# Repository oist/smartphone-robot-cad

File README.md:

# CAD for the OIST smartphone robots

This repository contains the CAD files for the OIST smartphone robots.

- [./body](./body) contains standard 3D CAD files used for the robot's 3D printed body.
- [./pcb](./pcb) contains the KiCad files for the robot's PCB and schematic design.

These two subprojects (body and pcb) have direct dependencies on each other as the 3D CAD design is based on the PCB design.
It is likely a good idea to manage the development of each on a separate branch and merge them together when necessary.

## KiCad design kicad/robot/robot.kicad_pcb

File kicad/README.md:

# Cloning the Repo
Currently this repo is an OIST internal repo, so read access is only given to specific users. Add external users for collaboration. 

Note this repo uses a central library management system. Symbols, footprints, and models are maintained on a personal fork of the central kicad library repos. These forks are maintained as submodules within the kicad-symbols, kicad-footprints, and kicad-packages3D respectively under:

[https://github.com/oist/smartphone-robot-cad/tree/main/kicad/](https://github.com/oist/smartphone-robot-cad/tree/main/kicad/)

Those forks should all be public and you should be able to clone the main repo with submodules without additional access, but just in case, here are the links to the forks:
- [https://gitlab.com/topherbuckley/kicad-symbols](https://gitlab.com/topherbuckley/kicad-symbols)
- [https://gitlab.com/topherbuckley/kicad-footprints](https://gitlab.com/topherbuckley/kicad-footprints)
- [https://gitlab.com/topherbuckley/kicad-packages3D](https://gitlab.com/topherbuckley/kicad-packages3D)

The easiest way to clone including all submodules would likely be `git clone --recurse-submodules -j8 git@github.com:oist/smartphone-robot-cad.git' if you are having trouble with that, you can refer to these links for details:

- [StackOverflow](https://stackoverflow.com/questions/3796927/how-do-i-git-clone-a-repo-including-its-submodules)
- [Git Docs](https://git-scm.com/docs/git-submodule)

Note that because of the main repo and submodules are hosted on two different platforms (github and gitlab) you must have credentials for both platforms. You can use your github credentials to setup a gitlab account and add your existing SSH keys to your gitlab account. More on how to do that [here](https://docs.gitlab.com/ee/user/ssh.html)

# Setting up the Environment

KiCAD makes use of user configuration files to define libraries, so without modifying your setup, you will unlikely be able to resolve the majority of libraries used in this project. There are many ways to go about this, of which you can find more details in the links below:

- [Project Collaboration Tips](https://forum.kicad.info/t/project-and-libary-setup-for-sharing-and-collaboration-kicad-version-5/20842/2) (See section Simplify First Time Setup...)

This repo has been set up to make using environmental variables the easiest option. In the `config` directory you will find a subdirectories corresponding to minor version of KiCAD. If you add an environment variable for KICAD_CONFIG_HOME pointing to this `config` directory, KiCAD will use these configuration files rather than the defaults. On Ubuntu 20.04 the default is `~/.config/kicad/`. Note you must then open kicad from a terminal that as properly sourced the newly created environmental variables. In a bash terminal this would be:

```
source KICAD_CONFIG_HOME=[path_to_repo]/config
kicad
```

Note this will use blank (default or empty)  configurations, so feel free to copy/paste your personal configurations into this `config` directory as all files other than `sym-lib-table` and `fp-lib-table` are ignored by the `.gitignore` file. 

# Additional References
- [Good discussion on KiCAD Collaboration and Versioning](https://forum.kicad.info/t/working-collaborately-on-projects-using-git/16114/11)
- [Nice tools for versioning](https://jnavila.github.io/plotkicadsch/)

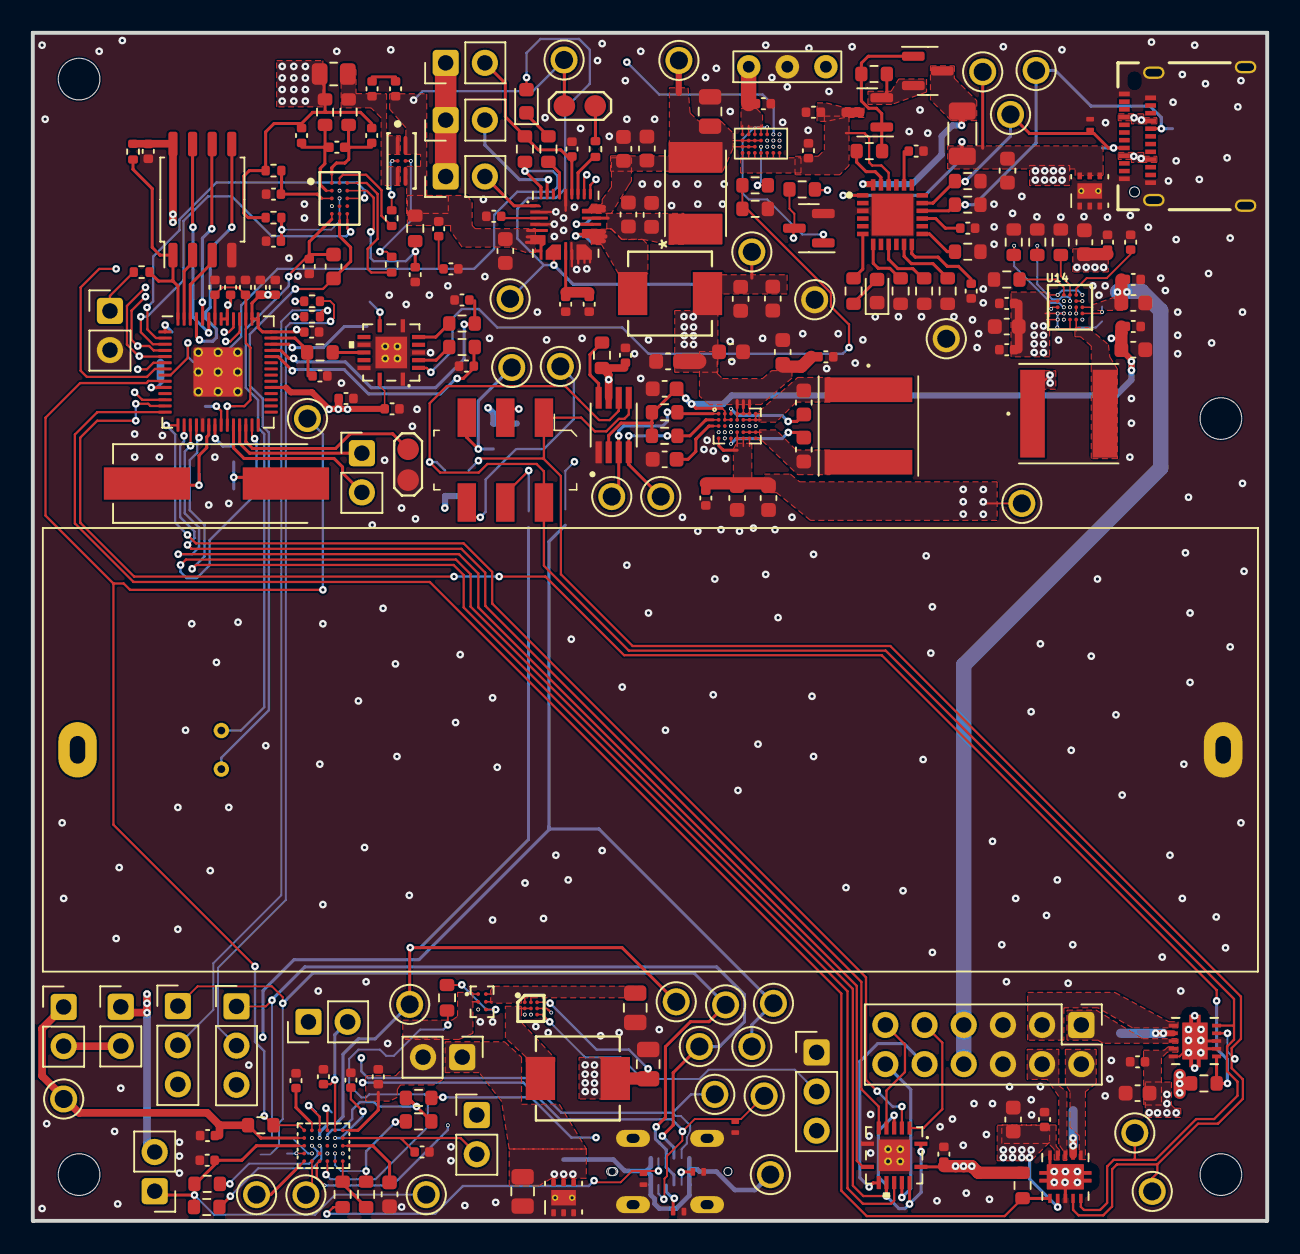
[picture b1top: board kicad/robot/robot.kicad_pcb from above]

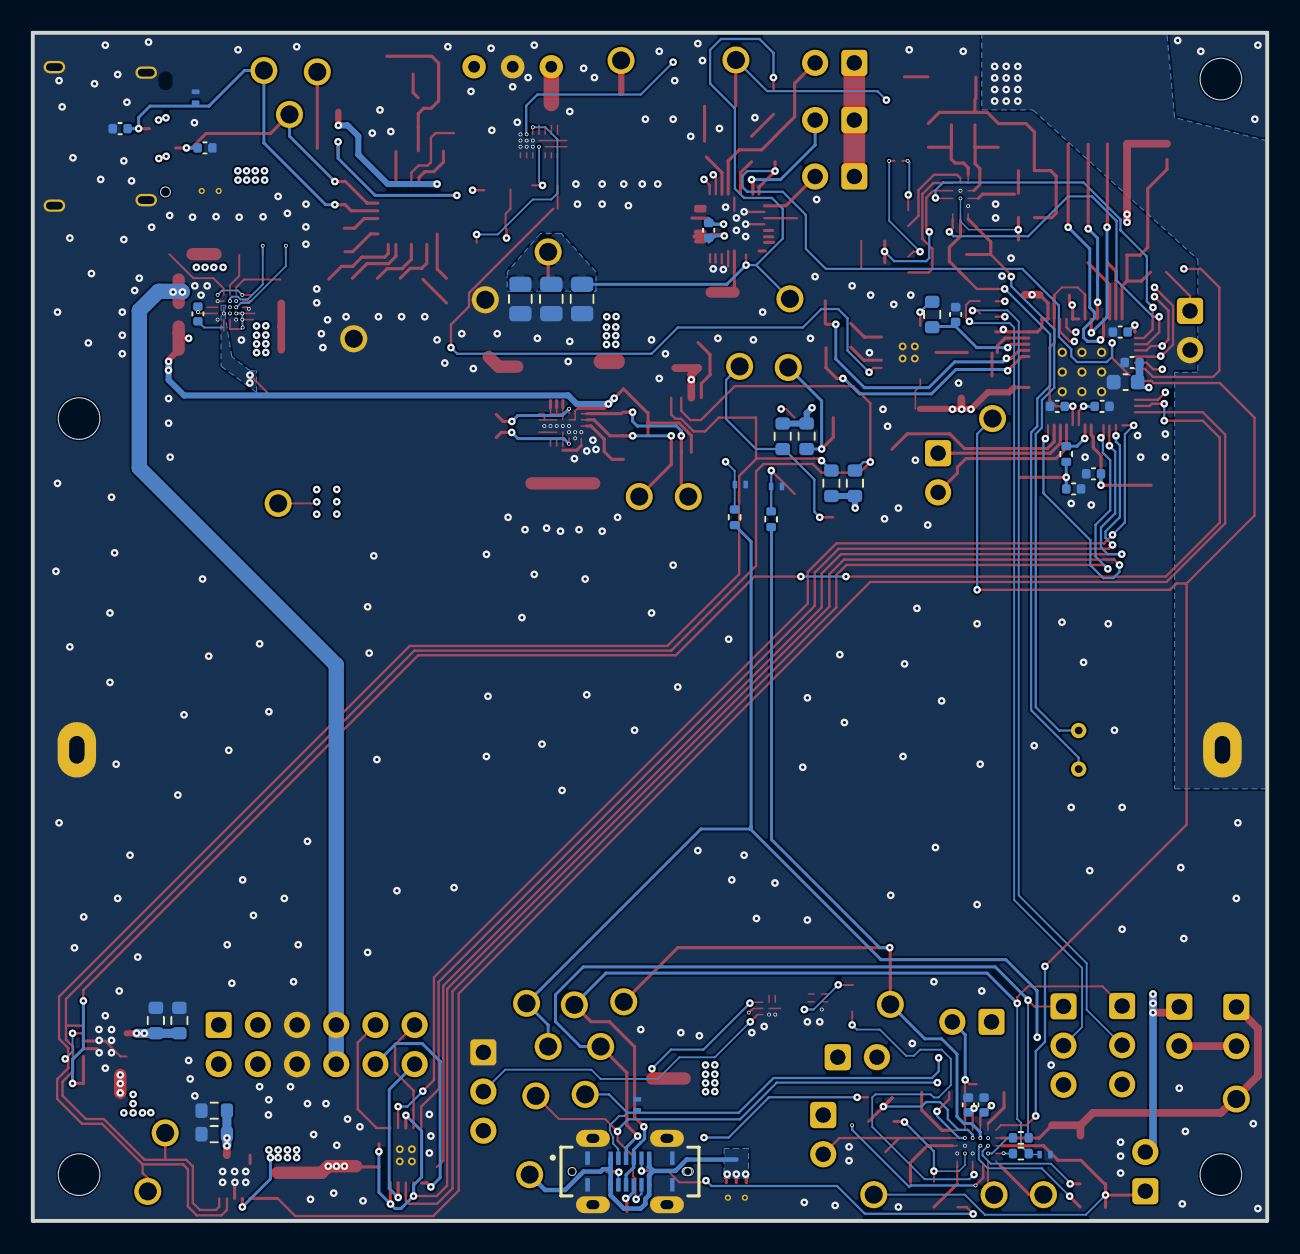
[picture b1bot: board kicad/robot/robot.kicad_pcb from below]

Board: 4 copper layers, 80.0 x 77.0 mm, 268 parts (37 on the bottom side), 159 nets.

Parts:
BT1: DNP; battery26650_holderOnly
BT2: DNP; battery26650
C1, C33, C34, C76, C78, C86, C87, C91, C93: 22uF; C_0603_1608Metric
C2, C3, C18, C19, C45, C46: 27pF; C_0402_1005Metric
C4, C8, C10, C21, C22, C29, C47, C48, C50, C51, C52, C53, C54, C55, C69, C88, C105: 1uF; C_0402_1005Metric
C5, C6, C7, C9, C11, C12, C13, C14, C15, C16, C24, C32, C35, C36, C37, C38, C39, C40, C41, C44, C57, C58, C59, C60, C61, C62, C63, C64, C65, C66, C70, C71, C72, C73, C74, C85, C90, C92, C102, C103, C104: 0.1uF; C_0402_1005Metric
C17, C20, C25, C27, C42, C43, C67, C68, C75, C77, C80: 10uF; C_0603_1608Metric
C23, C97, C100, C101: 4.7uF; C_0805_2012Metric
C26, C56: 0.47uF; C_0603_1608Metric
C28, C49: 2.2uF; C_0603_1608Metric
C30, C31: 0.22uF; C_0603_1608Metric
C81, C82, C83: DNP; C_0805_2012Metric
C84: 10nF; C_0402_1005Metric
D4: LED_B; D_0603_1608Metric_Harvatek
D6: LED_YG; D_0603_1608Metric_Harvatek
D7: D_Schottky; SD2114S040S8R0
H1, H2, H3, H4: MountingHole; MountingHole_2.7mm_M2.5
J1: USBC_Receptacle_SMD_RA; CON_USB3.1-C_RCPT_SMD_RA_ACP_12401610E4#2A
J3: 67996-412HLF; PinHeader_2x06_P2.54mm_Vertical
J4: USB4120-03-C_REVA; GCT_USB4120-03-C_REVA
JP1, JP2, JP3, JP4, JP5, JP6, JP7: Jumper_Bridged; 2.54mm_2pointJumperClosed
JP8, JP9: Jumper_Open; 2.54mm_2pointJumperOpen
JP10, JP11, JP12: Jumper_3_Bridged12; PinHeader_1x03_P2.54mm_Vertical_Pins12Connected
JP13, JP14, JP15, JP16, JP17, JP18, JP19, JP20, JP21, JP22: Jumper; 2.54mm_2pointJumper
L1, L3: 1.5uH; NRS6028T1R5NMGJ
L2, L4: 0.47uH; Vishay-IHLP-2020BZ-FP_1.905x2.79-3D_2.0-0-0-MFG
Q1: Q_NMOS_GDS; SOT-23
Q2: EFC8811R-TF; ON_Semiconductor-568AL-10_2013-O-MFG
Q3, Q4: YJL3416A; SOT-23
Q5, Q6: SN74AHC125RGYR
R1, R5, R46, R47, R50: 1k; R_0402_1005Metric
R2: DNP; R_0402_1005Metric
R3, R4: 27; R_0402_1005Metric
R6, R7, R32, R33, R41, R42: 10; R_0402_1005Metric
R10, R11, R14, R15, R20, R21, R34, R35: 2.2k; R_0603_1608Metric
R16: 510k; R_0603_1608Metric
R17, R49, R59, R60, R61: 100k; R_0603_1608Metric
R18: 47K; R_0603_1608Metric
R19, R36: 200k; R_0603_1608Metric
R22, R23, R24, R25, R58: 100; R_0603_1608Metric
R26, R27: DNP; R_0603_1608Metric
R28, R31, R66: 10k; R_0603_1608Metric
R29, R30: 0.39; R_0603_1608Metric
R37, R39: 649k; R_0603_1608Metric
R38, R40: 120k; R_0603_1608Metric
R43, R45: 200; R_0603_1608Metric
R44: 5m; R_0805_2012Metric
R48: 2k; R_0603_1608Metric
R51: 10m; R_1206_3216Metric
R52: 768k; R_0603_1608Metric
R53: 113K; R_0603_1608Metric
R54: 28k; R_0603_1608Metric
R55: 14k; R_0603_1608Metric
R56: 110; R_0603_1608Metric
R57: 360; R_0603_1608Metric
R62: 45.3k; R_0603_1608Metric
R63, R64: 5.1k; R_0603_1608Metric
R65: 10M; R_0603_1608Metric
S1: JS202011SCQN; Switch_Slide_JS202011SCQN
TH1: DNP; battery26650_thermistor
TP1, TP2, TP3, TP4, TP5, TP6, TP9, TP10, TP11, TP13, TP14, TP15, TP16, TP17, TP18, TP19, TP20, TP21, TP22, TP23, TP24, TP25, TP26, TP29, TP30, TP31, TP32, TP33, TP34, TP36: TP5002; KEYSTONE_5002
TP12, TP28: TP2PinPads; TestPoint_2Pads_Pitch2mm_SMD
TP27, TP35: 2PinHeader; PinHeader_1x02_P2.54mm_Vertical
U1: DNP; WRM483265-10F5-12V-G
U2: W25Q128JVS; SOIC-8_5.23x5.23mm_P1.27mm
U3: RP2040; RP2040-QFN-56
U4: NCP3901
U5: LSF0102DCTR; SOP65P400X130-8N
U6: MAX77857; WLP-35_7x5_2.828x2.028mm
U7, U10, U15, U19, U20, U21, U22, U23, U26, U27: TPD1E05U06; TPD1E05U06DPYR
U8, U9: DRV8830DRCR; IC_DRV8830DRCR
U11: MAX77958EWV+T; MAX77958EWV&plus_T
U12: BQ27742YZFR-G1; Texas_Instruments-YZF0015-0-0-MFG
U13: MAX77976EFD+; MAX77976
U14: MAX77642ANA+; Maxim-N252B2-1-0-A-MFG
U16: fpf1048bucx; BGA6N50P3X2_146X96X62N
U17: TPS61253AYFFT; Texas_Instruments-YFF0009-BGA9C40P3X3_119X129X62
U18: AP33771DKZ-13; AP33771DKZ13
U24, U25: TVS0500DRV; TVS0500DRVR
Y1: ABLS-12.000MHZ-B4-T; Crystal_SMD_HC49-US

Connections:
/1V8: C26.1, C74.1, C86.1, R20.1, R21.1, U5.2 (VREF_A), U6.A2 (VIO), U6.B2 (EN), U6.B3 (EN), U14.D3 (SBB2)
/3V3: C5.1, C9.1, C10.1, C11.1, C12.1, C13.1, C14.1, C15.1, C16.1, C17.1, C24.1, C35.1, C44.1, C92.1, C93.1, JP1.1 (A), JP5.2 (B), JP7.1 (A), JP8.1 (A), JP9.1 (A), JP10.3 (B), Q5.14 (VCC), Q6.14 (VCC), R2.1, R10.1, R11.1, R14.1, R15.1, R18.1, R19.1, R28.1, R31.1, U2.8 (VCC), U3.1 (IOVDD), U3.10 (IOVDD), U3.22 (IOVDD), U3.33 (IOVDD), U3.42 (IOVDD), U3.43 (ADC_AVDD), U3.44 (VREG_IN), U3.48 (USB_VDD), U3.49 (IOVDD), U5.7 (VREF_B), U14.C3 (SBB1)
/5V: C90.1, C91.1, J3.7, J3.8, U14.C5 (SBB0)
/ADC0: Q5.2 (1A), R16.2, R17.1
/Charger/BATT: C63.2, C65.1, C75.1, Q2.4 (SOURCE2), Q2.6 (SOURCE2), R48.1, TP12.2, TP24.1, U13.5 (BATSP), U13.6 (BATT), U13.7 (BATT), U13.8 (BATT)
/Charger/PVDD: C69.1, C70.1, U13.12 (PVDD)
/Charger/V_IN: C23.1, C67.1, C68.1, D7.2 (Anode), TP23.1, U4.B5 (OUT), U4.B6 (OUT), U4.B7 (OUT), U4.C4 (OUT), U4.C5 (OUT), U4.C6 (OUT), U4.C7 (OUT), U13.22 (CHGIN), U13.23 (CHGIN)
/GPIO4: Q1.3 (D), R18.2, U3.6 (GPIO4)
/GPIO5: U3.7 (GPIO5), U4.D2 (VINA_EN/OTG_EN)
/GPIO6: R49.2, U3.8 (GPIO6), U13.32 (IRQB)
/GPIO7: R36.2, TP20.1, U3.9 (GPIO7), U11.A1 (INTB)
/GPIO9: U1.3 (WC_EN), U3.12 (GPIO9)
/GPIO10: R28.2, U3.13 (GPIO10), U8.6 (~FAULT)
/GPIO11: R31.2, U3.14 (GPIO11), U9.6 (~FAULT)
/GPIO12: Q6.3 (1Y), U3.15 (GPIO12)
/GPIO13: Q6.6 (2Y), U3.16 (GPIO13)
/GPIO14: Q6.8 (3Y), U3.17 (GPIO14)
/GPIO15: Q6.11 (4Y), U3.18 (GPIO15)
/GPIO16: Q6.1 (1~OE), Q6.4 (2~OE), Q6.10 (3~OE), Q6.13 (4~OE), U3.27 (GPIO16)
/I2C0_SCL: R15.2, S1.4, TP4.1, U3.3 (GPIO1), U5.6 (B1), U8.10 (SCL), U9.10 (SCL), U12.E3 (SCL)
/I2C0_SDA: R14.2, S1.1, TP3.1, U3.2 (GPIO0), U5.5 (B2), U8.9 (SDA), U9.9 (SDA), U12.C3 (SDA)
/I2C1_SCL: R35.2, U3.5 (GPIO3), U11.C2 (SCL_M), U13.24 (SCL)
/I2C1_SDA: R34.2, U3.4 (GPIO2), U11.C3 (SDA_M), U13.25 (SDA)
/MCU/D+: JP12.2 (C), R3.1
/MCU/D-: JP11.2 (C), R4.1
/MCU/GPIO26_ADC0: C39.1, R25.1, U3.38 (GPIO26_ADC0)
/MCU/GPIO27_ADC1: C38.1, R24.1, U3.39 (GPIO27_ADC1)
/MCU/GPIO28_ADC2: C37.1, R23.1, U3.40 (GPIO28_ADC2)
/MCU/GPIO29_ADC3: C36.1, R22.1, U3.41 (GPIO29_ADC3)
/MCU/QSPI_SCLK: U2.6 (CLK), U3.52 (QSPI_SCLK)
/MCU/QSPI_SD0: U2.5 (DI(IO0)), U3.53 (QSPI_SD0)
/MCU/QSPI_SD1: U2.2 (DO(IO1)), U3.55 (QSPI_SD1)
/MCU/QSPI_SD2: U2.3 (IO2), U3.54 (QSPI_SD2)
/MCU/QSPI_SD3: U2.7 (IO3), U3.51 (QSPI_SD3)
/MCU/QSPI_SS: R1.1, R2.2, U2.1 (~CS), U3.56 (QSPI_SS)
/MCU/RUN: TP28.1, U3.26 (RUN)
/MCU/SWCLK: TP27.2, U3.24 (SWCLK)
/MCU/SWD: TP27.1, U3.25 (SWD)
/MCU/XIN: C2.1, U3.20 (XIN), Y1.1
/MCU/XOUT: R5.1, U3.21 (XOUT)
/MCU/~USB_BOOT: R1.2, TP35.1
/MOTORS/ENC_11: J3.9, Q6.2 (1A)
/MOTORS/ENC_12: J3.11, Q6.5 (2A)
/MOTORS/ENC_21: J3.10, Q6.9 (3A)
/MOTORS/ENC_22: J3.12, Q6.12 (4A)
/MOTORS/OUT_N1: J3.3, U8.1 (OUT2)
/MOTORS/OUT_N2: J3.2, U9.1 (OUT2)
/MOTORS/OUT_P1: J3.1, U8.3 (OUT1)
/MOTORS/OUT_P2: J3.4, U9.3 (OUT1)
/PowerMux/FLAG: Q1.1 (G), U4.D3 (VINB_EN/FLAG)
/PowerMux/VIN_A: C21.1, C105.1, Q4.3 (D), U4.A1 (VINA), U4.A2 (VINA), U4.A3 (VINA), U4.A4 (VINA), U4.A5 (VINA), U4.A6 (VINA), U4.A7 (VINA), U18.22 (VBUS)
/PowerMux/VIN_B: C22.1, U1.1 (Vchar_IN), U4.D4 (VINB), U4.D5 (VINB), U4.D6 (VINB), U4.D7 (VINB)
/SCL_EXT: R11.2, S1.6, TP6.1
/SCL_SL: R7.1, TP2.1, TP19.1, U11.B3 (SDA)
/SDA_EXT: R10.2, S1.3, TP5.1
/SDA_SL: R6.1, TP1.1, TP18.1, U11.B2 (SCL)
/SYS: C1.1, C4.1, C25.1, C27.1, C29.2, C76.1, C78.1, C81.1, C82.1, C83.1, C85.1, C87.1, C101.1, D6.2 (A), JP2.1 (A), JP3.1 (A), L2.2, L4.1, TP25.1, TP36.1, U6.A4 (IN), U6.A5 (IN), U6.A6 (IN), U6.B4 (IN), U13.9 (SYS), U13.10 (SYS), U13.11 (SYS), U14.A1 (SYSA), U14.A5 (IN_LDO), U14.B1 (SYSA), U14.D1 (EN1), U14.D2 (EN0), U14.E1 (EN2), U14.E3 (IN_SBB), U17.A3 (VIN)
/USB-PD-ExtChg/CC1: C18.1, J1.A5 (CC1), R63.1, TP9.1, U18.17 (CC1), U26.1 (I/O)
/USB-PD-ExtChg/CC2: C19.1, J1.B5 (CC2), R64.1, TP10.1, U18.16 (CC2), U27.1 (I/O)
/USB-PD-PhonePC/DN_EXT: J4.A7 (Dn1), J4.B7 (Dn2), JP11.1 (A), R32.1, TP13.1, U15.1 (I/O)
/USB-PD-PhonePC/DN_Switched: JP11.3 (B), TP16.1, U11.E1 (DN1)
/USB-PD-PhonePC/DP2_Switched: JP12.3 (B), TP17.1, U11.E2 (DP2)
/USB-PD-PhonePC/DP_EXT: J4.A6 (Dp1), J4.B6 (Dp2), JP12.1 (A), R33.1, TP14.1, U19.1 (I/O)
/USB-PD-PhonePC/GPIO0: R37.2, R38.1, U11.E6 (GPIO0)
/USB-PD-PhonePC/GPIO1: R39.2, R40.1, U11.B4 (GPIO1)
/USB-PD-PhonePC/GPIO3: R37.1, R39.1, U11.D5 (GPIO3)
/USB-PD-PhonePC/GPIO4: R65.2, U11.E4 (GPIO4)
/USB-PD-PhonePC/GPIO5: U11.E3 (GPIO5), U17.B3 (EN)
/USB-PD-PhonePC/VIO1: JP1.2 (B), JP6.2 (B)
/USB-PD-PhonePC/VIO1_: C54.1, JP6.1 (A), R36.1, TP22.1, U11.B1 (VIO1)
/USB-PD-PhonePC/VIO2_: C53.1, JP5.1 (A), R34.1, R35.1, TP21.1, U11.C1 (VIO2)
/VBoost: C32.2, C33.2, C34.2, C40.1, C41.1, C42.1, C43.1, TP34.1, U6.D4 (OUT), U6.E1 (FB), U6.E4 (OUT), U6.E5 (OUT), U6.E6 (OUT), U8.4 (VCC), U9.4 (VCC), U9.7 (A0)
GND: BT1.2 (-), C1.2, C2.2, C3.2, C4.2, C5.2, C6.2, C7.2, C8.2, C9.2, C10.2, C11.2, C12.2, C13.2, C14.2, C15.2, C16.2, C17.2, C18.2, C19.2, C20.2, C21.2, C22.2, C23.2, C24.2, C25.2, C26.2, C27.2, C28.2, C29.1, C32.1, C33.1, C34.1, C35.2, C36.2, C37.2, C38.2, C39.2, C40.2, C41.2, C42.2, C43.2, C44.2, C45.2, C46.2, C47.2, C48.2, C49.2, C50.2, C51.2, C52.2, C53.2, C54.2, C55.2, C57.2, C58.2, C64.2, C66.2, C67.2, C68.2, C69.2, C70.2, C71.2, C72.2, C74.2, C75.2, C76.2, C77.2, C78.2, C80.2, C81.2, C82.2, C83.2, C85.2, C86.2, C87.2, C88.2, C90.2, C91.2, C92.2, C93.2, C97.2, C100.2, C101.2, C102.2, C103.2, C104.2, C105.2, D4.1 (K), J1.25 (SHLD), J1.A1 (GND), J1.A12 (GND), J1.B1 (GND), J1.B12 (GND), J3.5, J3.6, J4.A1 (GND), J4.A12 (GND), J4.B1 (GND), J4.B12 (GND), J4.SHELL, JP10.1 (A), Q1.2 (S), Q5.1 (1~OE), Q5.4 (2~OE), Q5.7 (GND), Q5.10 (3~OE), Q5.13 (4~OE), Q5.PAD (GND), Q6.7 (GND), Q6.PAD (GND), R17.2, R26.2, R27.2, R29.2, R30.2, R52.2, R53.2, R54.2, R55.2, R59.1, R60.1, R61.1, R62.2, R63.2, R64.2, TP26.1, TP28.2, TP33.1, TP35.2, U1.2 (GND), U2.4 (GND), U3.19 (TESTEN), U3.57 (GND), U4.B1 (GND), U4.B2 (GND), U4.B3 (GND), U4.C1 (MODE), U4.C2 (GND), U4.C3 (GND), U4.D1 (CRTL), U5.1 (GND), U6.C3 (PGND), U6.C4 (PGND), U6.C5 (PGND), U6.C6 (PGND), U6.C7 (PGND), U6.D1 (SEL), U6.D2 (PGND), U6.D3 (PGND), U6.E2 (AGND), U7.2 (GND), U8.5 (GND), U8.7 (A0), U8.8 (A1), U8.11 (GND), U9.5 (GND), U9.8 (A1), U9.11 (GND), U10.2 (GND), U11.C5 (GND_A), U11.D4 (GPIO6_I2C_ADDR), U11.D6 (GND_D), U12.B2 (NC), U12.D1 (VSS), U13.2 (THM), U13.4 (BATSN), U13.13 (DGND), U13.14 (PGND), U13.15 (PGND), U13.16 (PGND), U13.28 (AGND), U14.B2 (RSET_LDO), U14.B4 (GND), U14.B5 (GND), U14.C1 (ENLDO), U14.E2 (GND), U14.E5 (PGND), U15.2 (GND), U16.C1 (GND), U17.C1 (GND), U17.C2 (GND), U18.3 (GND), U18.25 (EP), U19.2 (GND), U20.2 (GND), U21.2 (GND), U22.2 (GND), U23.2 (GND), U24.1 (GND), U24.2 (GND), U24.3 (GND), U24.7 (GND), U25.1 (GND), U25.2 (GND), U25.3 (GND), U25.7 (GND), U26.2 (GND), U27.2 (GND)
unnamed: BT1.1 (+), C59.2, C61.1, R41.1, R42.1, R43.2, R44.2
unnamed: C3.1, R5.2, Y1.2
unnamed: C6.1, C7.1, C8.1, U3.23 (DVDD), U3.45 (VREG_VOUT), U3.50 (DVDD)
unnamed: C20.1, J1.A4 (VBUS), J1.A9 (VBUS), J1.B4 (VBUS), J1.B9 (VBUS), R51.1, TP11.1, U18.1 (ISENP), U25.4 (IN), U25.5 (IN), U25.6 (IN)
unnamed: C28.1, U6.C1 (VL)
unnamed: C30.1, U6.A3 (BST1)
unnamed: C30.2, L1.1, U6.A7 (LX1), U6.B5 (LX1), U6.B6 (LX1), U6.B7 (LX1)
unnamed: C31.1, L1.2, U6.D5 (LX2), U6.D6 (LX2), U6.D7 (LX2), U6.E7 (LX2)
unnamed: C31.2, U6.E3 (BST2)
unnamed: C45.1, J4.B5 (CC2), TP29.1, U11.A4 (CC2), U22.1 (I/O)
unnamed: C46.1, J4.A5 (CC1), TP15.1, U11.A3 (CC1), U23.1 (I/O)
unnamed: C47.1, JP2.2 (B), U11.A5 (VCIN)
unnamed: C48.1, JP3.2 (B), U11.B6 (SYS)
unnamed: C49.1, U11.C6 (AVL)
unnamed: C50.1, JP4.2 (B), U11.A6 (VBUS), U16.A1 (VOUT), U16.B1 (VOUT)
unnamed: C51.1, U11.A2 (VDD1P1)
unnamed: C52.1, U11.B5 (VDD1P8)
unnamed: C55.1, C56.1, TH1.1, U12.E1 (REG25)
unnamed: C56.2, TH1.2, U12.E2 (TS)
unnamed: C57.1, R42.2, U12.C2 (BAT)
unnamed: C58.1, R41.2, U12.C1 (VPWR)
unnamed: C59.1, C60.1, R43.1, U12.B1 (SRN)
unnamed: C60.2, C61.2, R45.1, U12.A1 (SRP)
unnamed: C62.1, Q2.1 (SOURCE1), Q2.3 (SOURCE1), R44.1, R45.2
unnamed: C62.2, C63.1
unnamed: C64.1, R48.2, U12.B3 (PACKP)
unnamed: C65.2, C66.1
unnamed: C71.1, JP7.2 (B), R49.1, U13.27 (VIO)
unnamed: C72.1, U13.3 (VDD)
unnamed: C73.1, U13.20 (BST)
unnamed: C73.2, L2.1, U13.17 (LX), U13.18 (LX), U13.19 (LX)
unnamed: C77.1, C80.1, D7.1 (Cathode), U13.21 (BYP)
unnamed: C84.1, L3.1, U14.C4 (LXB), U14.D4 (LXB)
unnamed: C84.2, U14.D5 (BST)
unnamed: C88.1, U14.A4 (LDO)
unnamed: C97.1, J4.A4 (VBUS), J4.A9 (VBUS), J4.B4 (VBUS), J4.B9 (VBUS), JP4.1 (A), TP30.1, U24.4 (IN), U24.5 (IN), U24.6 (IN)
unnamed: C100.1, U16.A2 (VIN), U16.B2 (VIN), U17.A1 (VOUT), U17.A2 (VOUT)
unnamed: C102.1, U18.12 (V3VD)
unnamed: C103.1, U18.20 (V5V)
unnamed: C104.1, U18.15 (IFB)
unnamed: D4.2 (A), R57.2
unnamed: D6.1 (K), R56.1
unnamed: J4.A8 (SBU1), R38.2, U21.1 (I/O)
unnamed: J4.B8 (SBU2), R40.2, U20.1 (I/O)
unnamed: JP8.2 (B), U13.31 (SUSPND)
unnamed: JP9.2 (B), U13.1 (DISQBAT)
unnamed: JP10.2 (C), U17.C3 (MODE)
unnamed: L3.2, U14.E4 (LXA)
unnamed: L4.2, U17.B1 (SW), U17.B2 (SW)
unnamed: Q2.2 (GATE1), R46.1
unnamed: Q2.5 (GATE2), R47.1
unnamed: Q3.1 (G), Q4.1 (G), R58.1, R66.2
unnamed: Q3.2 (S), Q4.2 (S), R66.1
unnamed: Q3.3 (D), R51.2, U18.24 (VCC)
unnamed: Q5.3 (1Y), R25.2
unnamed: Q5.6 (2Y), R24.2
unnamed: Q5.8 (3Y), R23.2
unnamed: Q5.11 (4Y), R22.2
unnamed: R3.2, U3.47 (USB_DP)
unnamed: R4.2, U3.46 (USB_DM)
unnamed: R6.2, S1.2, U7.1 (I/O)
unnamed: R7.2, S1.5, U10.1 (I/O)
unnamed: R16.1, U4.B4 (VINA_S)
unnamed: R19.2, U5.8 (EN)
unnamed: R20.2, TP32.1, U5.4 (A2), U6.B1 (SDA)
unnamed: R21.2, TP31.1, U5.3 (A1), U6.A1 (SCL)
unnamed: R26.1, R29.1, U8.2 (ISENSE)
unnamed: R27.1, R30.1, U9.2 (ISENSE)
unnamed: R32.2, U11.D1 (DN)
unnamed: R33.2, U11.D2 (DP)
unnamed: R46.2, U12.A2 (CHG)
unnamed: R47.2, U12.A3 (DSG)
unnamed: R50.1, U13.26 (EXTSM)
unnamed: R50.2, TP12.1
unnamed: R52.1, U14.B3 (RSET_SBB0)
unnamed: R53.1, U14.A3 (RSET_SBB1)
unnamed: R54.1, U14.A2 (RSET_SBB2)
unnamed: R55.1, U14.C2 (RSET_IPK)
unnamed: R56.2, U13.29 (STAT)
unnamed: R57.1, U18.6 (GPIO4)
unnamed: R58.2, U18.23 (PWR_EN)
unnamed: R59.2, U18.7 (VSEL1)
unnamed: R60.2, U18.9 (VSEL0)
unnamed: R61.2, U18.11 (VSEL2)
unnamed: R62.1, U18.13 (PSEL)
unnamed: R65.1, U16.C2 (ON)

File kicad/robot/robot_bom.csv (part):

Ref	Qty Single Board	Batch Size	Qty Total Batch	Stock	Spares	Total+Spares	Sending	Need to Buy	Value	Manufacturer	Part Number	Description	Footprint	Type
Q5,Q6	2	5	10	50	1	11	50	0	SN74AHC125RGYR	Texas Instruments	SN74AHC125RGYR	Buffer/Line Driver 4-CH Non-Inverting 3-ST CMOS 14-Pin VQFN EP T/R	Ultra_Librarian:SN74AHC125RGYR	
U8,U9	2	5	10	30	1	11	25	0	DRV8830DRCR	Texas Instruments	DRV8830DRCR	DC Motor Driver I2C Control	Snapeda:IC_DRV8830DRCR	
Q2	1	5	5	25	1	6	25	0	EFC8811R-TF	ON Semiconductor	EFC8811R-TF	EFC8811R-TF	custom_transistors:ON_Semiconductor-568AL-10_2013-O-MFG	
U4	1	5	5	25	1	6	25	0	NCP3901	onsemi	NCP3901		custom_modules:NCP3901	
U5	1	5	5	25	1	6	25	0	LSF0102DCTR	Texas Instruments	LSF0102DCTR	Dual bidirectional multi-voltage level translator	Snapeda:SOP65P400X130-8N	
U6	1	5	5	25	1	6	25	0	MAX77857	Maxim	MAX77857		Package_BGA:WLP-35_7x5_2.828x2.028mm	
U11	1	5	5	25	1	6	25	0	MAX77958EWV+T	Maxim	MAX77958EWV+T	USB-PD Controller	Ultra_Librarian:MAX77958EWV&plus_T	
U12	1	5	5	25	1	6	25	0	BQ27742YZFR-G1	Texas Instruments	BQ27742YZFR-G1	BQ27742YZFR-G1	Package_BGA:Texas_Instruments-YZF0015-0-0-MFG	
U13	1	5	5	25	1	6	25	0	MAX77976EFD+	Maxim	MAX77976EFD+		Ultra_Librarian:MAX77976	
U14	1	5	5	25	1	6	25	0	MAX77642ANA+	Maxim	MAX77642ANA+	MAX77642ANA+	Package_BGA:Maxim-N252B2-1-0-A-MFG	
U18	1	5	5	25	1	6	25	0	AP33771DKZ-13	Diodes Inc.	AP33771DKZ-13	Diodes Inc. ACDC Decoder W-QFN4040-24 T&R 3K	Package_DFN_QFN:AP33771DKZ13	
BT1	0	5	0	0	0	0		0	DNP	Uxcell	a15042300ux0145		custom_modules:battery26650_holderOnly	
BT2	0	5	0	0	0	0		0	DNP	Suprise Collection	26650-5000-1	Single-cell battery	custom_modules:battery26650	
C1,C33,C34,C76,C78,C86,C87,C91,C93	9	5	45	0	5	50		45	22uF	Murata	GRM188R61A226ME15D	Unpolarized capacitor	Capacitor_SMD:C_0603_1608Metric	
C2,C3,C18,C19,C45,C46	6	5	30	0	3	33		30	27pF	Murata	GRM1555C1H270JA01J	Unpolarized capacitor	Capacitor_SMD:C_0402_1005Metric	
C4,C8,C10,C21,C22,C29,C47,C48,C50,C51,C52,C53,C54,C55,C69,C88,C105	17	5	85	0	9	94		85	1uF	Murata	GRM155R61E105KA12D	Unpolarized capacitor	Capacitor_SMD:C_0402_1005Metric	
C5,C6,C7,C9,C11,C12,C13,C14,C15,C16,C24,C32,C35,C36,C37,C38,C39,C40,C41,C44,C57,C58,C59,C60,C61,C62,C63,C64,C65,C66,C70,C71,C72,C73,C74,C85,C90,C92,C102,C103,C104	41	5	205	0	21	226		205	0.1uF	Samsung	CL05A104KA5NNNC	Unpolarized capacitor	Capacitor_SMD:C_0402_1005Metric	
C17,C20,C25,C27,C42,C43,C67,C68,C75,C77,C80	11	5	55	0	6	61		55	10uF	Murata	GRM188R61E106KA73J	Unpolarized capacitor	Capacitor_SMD:C_0603_1608Metric	
C23,C97,C100,C101	4	5	20	0	2	22		20	4.7uF	Samsung	CL21A475KAQNNNG	Unpolarized capacitor	Capacitor_SMD:C_0805_2012Metric	
C26,C56	2	5	10	0	1	11		10	0.47uF	Samsung	CL10B474KO8NNNC	Unpolarized capacitor	Capacitor_SMD:C_0603_1608Metric	
C28,C49	2	5	10	0	1	11		10	2.2uF	Samsung	CL10A225KP8NNNC	Unpolarized capacitor	Capacitor_SMD:C_0603_1608Metric	
C30,C31	2	5	10	0	1	11		10	0.22uF	Samsung	CL10B224KA8NNNC	Unpolarized capacitor	Capacitor_SMD:C_0603_1608Metric	
C79	0	5	0	0	0	0		0	DNP	DNP	DNP	Unpolarized capacitor	Capacitor_SMD:C_0805_2012Metric	
C84	1	5	5	0	1	6		5	10nF	Samsung	CL05B103KA5NNNC	Unpolarized capacitor	Capacitor_SMD:C_0402_1005Metric	
D4	1	5	5	0	1	6		5	LED_B	Harvatek	B0211NB--02D000114U1930	Light emitting diode	Diode_SMD:D_0603_1608Metric_Harvatek	
D6	1	5	5	0	1	6		5	LED_YG	Harvatek	B1911UYG-20D000114U1930	Light emitting diode	Diode_SMD:D_0603_1608Metric_Harvatek	
D7	1	5	5	0	1	6		5	D_Schottky	KYOCERA AVX	SD2114S040S8R0		Diode_SMD:SD2114S040S8R0	
H1,H2,H3,H4	4	5	20	0	2	22		20	MountingHole	N/A	N/A	Mounting Hole without connection	MountingHole:MountingHole_2.7mm_M2.5	
J1	1	5	5	0	1	6		5	USBC_Receptacle_SMD_RA	Amphenol Commercial Products	12401610E4#2A		AltiumImports:CON_USB3.1-C_RCPT_SMD_RA_ACP_12401610E4#2A	
J3	1	5	5	0	1	6		5	67996-412HLF	Amphenol ICC (FCI)	67996-412HLF	CONN HEADER VERT 12POS 2.54MM	Connector_PinHeader_2.54mm:PinHeader_2x06_P2.54mm_Vertical	
J4	1	5	5	0	1	6		5	USB4120-03-C_REVA	GCT	USB4120-03-C		Connector_USB:GCT_USB4120-03-C_REVA	
JP1,JP2,JP3,JP4,JP5,JP6,JP7	7	5	35	0	4	39		35	Jumper_Bridged	Adam Tech	PH1-02-UA	Jumper, 2-pole, closed/bridged	custom_connectors:2.54mm_2pointJumperClosed	
JP8,JP9	2	5	10	0	1	11		10	Jumper_Open	Adam Tech	PH1-02-UA	Jumper, 2-pole, open	custom_connectors:2.54mm_2pointJumperOpen	
JP10,JP11,JP12	3	5	15	0	2	17		15	Jumper_3_Bridged12	Molex	22-28-4030	Jumper, 3-pole, pins 1+2 closed/bridged	Connector_PinHeader_2.54mm:PinHeader_1x03_P2.54mm_Vertical_Pins12Connected	
JP13,JP14,JP15,JP16,JP17,JP18,JP19,JP20,JP21,JP22	10	5	50	0	5	55		50	Jumper	Sullins	QPC02SXGN-RC	Mechanical Jumper	custom_connectors:2.54mm_2pointJumper	
L1,L3	2	5	10	0	1	11		10	1.5uH	TAIYO YUDEN	NRS6028T1R5NMGJ	Inductor	custom_inductors:NRS6028T1R5NMGJ	
L2,L4	2	5	10	0	1	11		10	0.47uH	Vishay	IHLP2020BZERR47M01	Inductor symbol for simulation only	custom_inductors:Vishay-IHLP-2020BZ-FP_1.905x2.79-3D_2.0-0-0-MFG	
Q1	1	5	5	0	1	6		5	Q_NMOS_GDS	Toshiba	T2N7002AK,LM	N-MOSFET transistor, gate/source/drain	Package_TO_SOT_SMD:SOT-23	
Q3,Q4	2	5	10	0	1	11		10	YJL3416A	Yangjie Electronic Technology 	YJL3416A	20V Vds, 0.63 Id, N-Channel MOSFET with ESD protection, SOT-523	Package_TO_SOT_SMD:SOT-23	
R1,R5,R46,R47,R50	5	5	25	0	3	28		25	1k	Walsin Technologies	WR04X102 JTL	Resistor	Resistor_SMD:R_0402_1005Metric	
R3,R4	2	5	10	0	1	11		10	27	Stackpole Electronics	RMCF0402JT27R0	Resistor	Resistor_SMD:R_0402_1005Metric	
R6,R7,R32,R33,R41,R42	6	5	30	0	3	33		30	10	Yageo	RC0402FR-1310RL	Resistor	Resistor_SMD:R_0402_1005Metric	
R10,R11,R14,R15,R20,R21,R34,R35	8	5	40	0	4	44		40	2.2k	Stackpole Electronics	RMCF0603JT2K20	Resistor	Resistor_SMD:R_0603_1608Metric	
R16	1	5	5	0	1	6		5	510k	Stackpole Electronics	RMCF0603JT510K	Resistor	Resistor_SMD:R_0603_1608Metric	
R17,R49,R59,R60,R61	5	5	25	0	3	28		25	100k	Stackpole Electronics	RMCF0603JG100K	Resistor	Resistor_SMD:R_0603_1608Metric	
R18	1	5	5	0	1	6		5	47K	Stackpole Electronics	RMCF0603JT47K0	Resistor	Resistor_SMD:R_0603_1608Metric	
R19,R36	2	5	10	0	1	11		10	200k	Stackpole Electronics	RMCF0603JT200K	Resistor	Resistor_SMD:R_0603_1608Metric	
R22,R23,R24,R25,R58	5	5	25	0	3	28		25	100	Stackpole Electronics	RMCF0603JT100R	Resistor	Resistor_SMD:R_0603_1608Metric	
R28,R31,R66	3	5	15	0	2	17		15	10k	Stackpole Electronics	RMCF0603JT10K0	Resistor	Resistor_SMD:R_0603_1608Metric	
R29,R30	2	5	10	0	1	11		10	0.39	Panasonic	ERJ-3RQJR39V	Resistor	Resistor_SMD:R_0603_1608Metric	
R37,R39	2	5	10	0	1	11		10	649k	Stackpole Electronics	RMCF0603FT649K	Resistor	Resistor_SMD:R_0603_1608Metric	
R38,R40	2	5	10	0	1	11		10	120k	Stackpole Electronics	RMCF0603JT120K	Resistor	Resistor_SMD:R_0603_1608Metric	
R43,R45	2	5	10	0	1	11		10	200	Bourns	CR0402-JW-201GLF	Resistor	Resistor_SMD:R_0603_1608Metric	
R44	1	5	5	0	1	6		5	5m	Yageo	PA0805FRF470R005L	Resistor	Resistor_SMD:R_0805_2012Metric	
R48	1	5	5	0	1	6		5	2k	Stackpole Electronics	RMCF0603FT2K00	Resistor	Resistor_SMD:R_0603_1608Metric	
R51	1	5	5	0	1	6		5	10m	Panasonic	ERJ-8CWJR010V	Resistor	Resistor_SMD:R_1206_3216Metric	
R52	1	5	5	0	1	6		5	768k	Stackpole Electronics	RMCF0603FT768K	Resistor	Resistor_SMD:R_0603_1608Metric	
R53	1	5	5	0	1	6		5	113K	Stackpole Electronics	RMCF0603FT113K	Resistor	Resistor_SMD:R_0603_1608Metric	
R54	1	5	5	0	1	6		5	28k	Stackpole Electronics	RMCF0603FT28K0	Resistor	Resistor_SMD:R_0603_1608Metric	
R55	1	5	5	0	1	6		5	14k	Stackpole Electronics	RMCF0603FT14K0	Resistor	Resistor_SMD:R_0603_1608Metric	
R56	1	5	5	0	1	6		5	110	Yageo	RC0603JR-07110RL	Resistor	Resistor_SMD:R_0603_1608Metric	
R57	1	5	5	0	1	6		5	360	Stackpole Electronics, Inc.	RMCF0603JT360R	Resistor	Resistor_SMD:R_0603_1608Metric	
R62	1	5	5	0	1	6		5	45.3k	Stackpole Electronics	RMCF0603FT45K3	Resistor	Resistor_SMD:R_0603_1608Metric	
R63,R64	2	5	10	0	1	11		10	5.1k	Stackpole Electronics	RMCF0603JT5K10	Resistor	Resistor_SMD:R_0603_1608Metric	
R65	1	5	5	0	1	6		5	10M	Yageo	AC0603JR-0710ML	Resistor	Resistor_SMD:R_0603_1608Metric	
S1	1	5	5	0	1	6		5	JS202011SCQN	C&K	JS202011SCQN	SWITCH SLIDE DPDT 300MA 6V	Button_Switch_SMD:Switch_Slide_JS202011SCQN	
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
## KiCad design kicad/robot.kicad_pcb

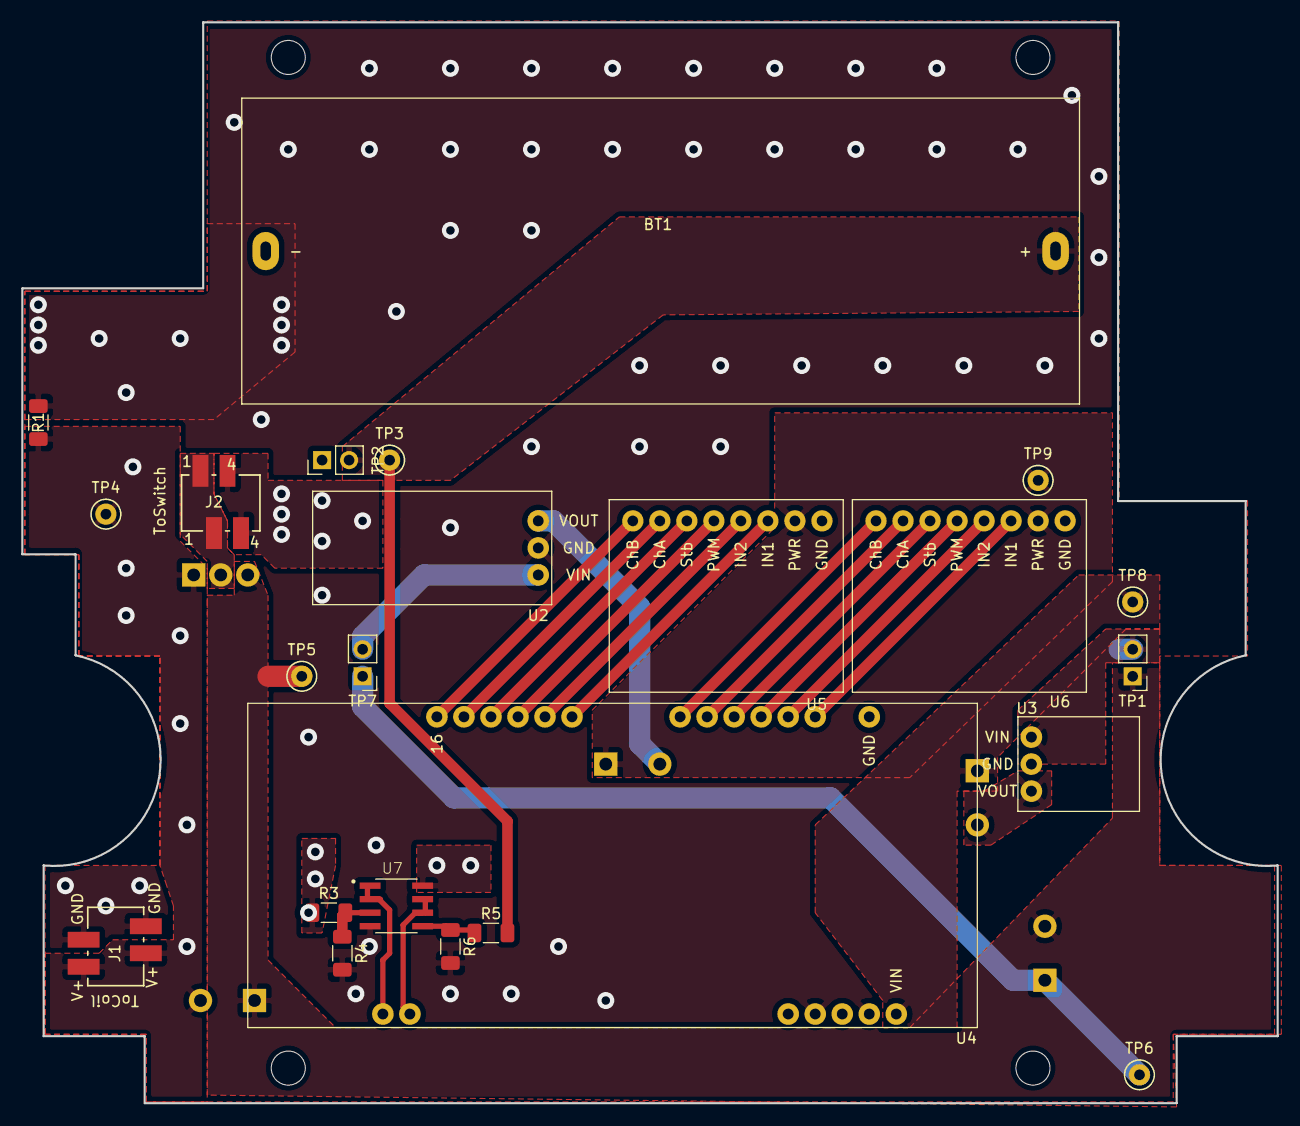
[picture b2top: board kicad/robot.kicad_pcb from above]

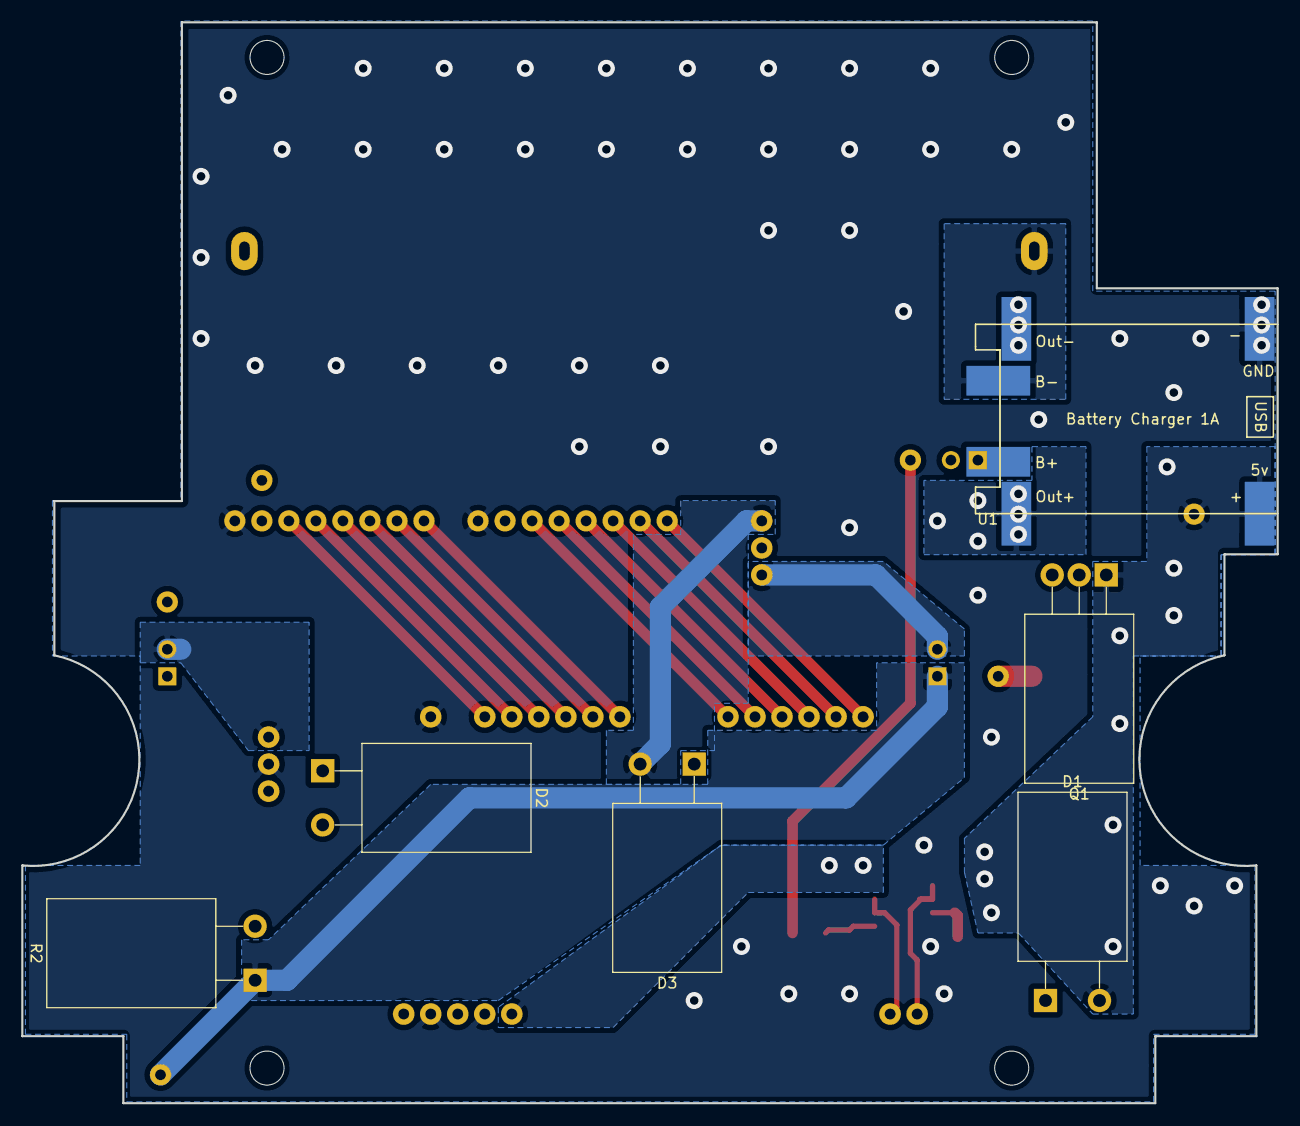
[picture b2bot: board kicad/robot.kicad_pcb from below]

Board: 2 copper layers, 118.0 x 101.6 mm, 29 parts (6 on the bottom side), 32 nets.

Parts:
BT1: 4.2V; battery26650
D1, D2, D3: STPS10L25D; TO-220-2_Horizontal_TabDown_NoHole
J1, J2: 188275-4
Q1: SQP90P06-07L; TO-220-3_Horizontal_TabDown_NoHole
R1: 100k; R_1206_3216Metric_Pad1.30x1.75mm_HandSolder
R2: 1; TO-220-2_Horizontal_TabDown_NoHole
R3: 137k; R_1206_3216Metric_Pad1.30x1.75mm_HandSolder
R4: 267k; R_1206_3216Metric_Pad1.30x1.75mm_HandSolder
R5: 102k; R_1206_3216Metric_Pad1.30x1.75mm_HandSolder
R6: 374k; R_1206_3216Metric_Pad1.30x1.75mm_HandSolder
TP1, TP2, TP7: TestPoint_CurrentShunt; 2.54mm_2pointCurrentTestPoint
TP3, TP4, TP5, TP6, TP8, TP9: TestPoint_keystone; TestPoint_Keystone_5000-5004_Miniature
U1: tp4056; TP4056-18650_SMD
U2: pololu_791
U3: pololu_2564
U4: ioio_header
U5, U6: hubeeBreakout
U7: TLV9002IDR; SOIC127P599X175-8N

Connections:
/3v3: U4.47, U7.8
/BatteryGauge: U4.34, U7.6, U7.7
/ChargerGauge: U4.33, U7.1, U7.2
/ChargerVoltage: R3.2, R4.1, U7.3
GND: J1.3, J1.4, R1.2, R4.2, R6.2, U1.2, U1.4, U2.2, U3.2, U4.50, U5.1, U6.1, U7.4
unnamed: BT1.1, R5.2, TP2.2, TP3.1
unnamed: BT1.2, U1.6
unnamed: D1.1, Q1.3, R2.2, TP1.1, TP5.1
unnamed: D1.2, J1.1, J1.2, Q1.1, R1.1, R3.1, TP4.1, U1.1
unnamed: D2.1, TP8.1, U4.49
unnamed: D2.2, U3.3
unnamed: D3.1, TP9.1, U5.2, U6.2
unnamed: D3.2, U2.3
unnamed: J2.1, J2.2, Q1.2
unnamed: J2.3, J2.4, U1.3
unnamed: R2.1, TP6.1, TP7.1
unnamed: R5.1, R6.1, U7.5
unnamed: TP1.2, U3.1
unnamed: TP2.1, U1.5
unnamed: TP7.2, U2.1
unnamed: U4.2, U6.3
unnamed: U4.3, U6.4
unnamed: U4.4, U6.5
unnamed: U4.5, U6.6
unnamed: U4.6, U6.7
unnamed: U4.7, U6.8
unnamed: U4.11, U5.3
unnamed: U4.12, U5.4
unnamed: U4.13, U5.5
unnamed: U4.14, U5.6
unnamed: U4.15, U5.7
unnamed: U4.16, U5.8

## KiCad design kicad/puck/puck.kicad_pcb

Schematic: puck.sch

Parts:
J1: PicoBlade_5Pin_SMD_Horizontal; Molex_PicoBlade_53261-0571_1x05-1MP_P1.25mm_Horizontal; Digi-Key Part Number WM7623CT-ND
J2: PicoBlade_2Pin_SMD_Horizontal; Molex_PicoBlade_53261-0271_1x02-1MP_P1.25mm_Horizontal; Digi-Key Part Number WM7620CT-ND
Q1, Q2: DMN3018SSD-13; SOIC127P600X170-8N; PARTREV 5-2; Digi-Key Part Number DMN3018SSD-13DICT-ND
Q3: IRLR6225TRPBF; TO-252-3; Digi-Key Part Number IRLR6225TRPBFCT-ND
TP8, TP9, TP10, TP11: TestPoint_CurrentShunt; SAMTEC_TSM-102-01-T-SH; Digi-Key Part Number SAM10785-ND
U2: SeeeduinoXIAO; Seeeduino_XIAO-MOUDLE14P-2p54-21X17p8MM; Digi-Key Part Number 1597-102010328-ND

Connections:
+5V: Q3.4, TP10.1, TP11.1, U2.13
/12vRegulator/Vin: TP11.2; also elsewhere on the board
/12vRegulator/Vout: TP8.2; also elsewhere on the board
/currentSense/IN+: TP9.1; also elsewhere on the board
/currentSense/OUT: U2.7; also elsewhere on the board
/currentSense/VS: TP10.2; also elsewhere on the board
GND: J2.2, Q1.1, Q1.3, Q2.1, Q2.3, U2.12; also elsewhere on the board
LED_B: J1.4, Q2.5, Q2.6
LED_B_IO: Q2.4, U2.2
LED_G: J1.3, Q1.7, Q1.8
LED_G_IO: Q1.2, U2.1
LED_R: J1.2, Q1.5, Q1.6
LED_R_IO: Q1.4, U2.0
LED_W: J1.5, Q2.7, Q2.8
LED_W_IO: Q2.2, U2.3
unnamed: J1.1, TP8.1
unnamed: Q3.1, U2.10
unnamed: Q3.3, TP9.2
SHDN: U2.6; also elsewhere on the board
WirelssModule_Vin: J2.1; also elsewhere on the board

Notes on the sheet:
To Wireless Charging External Unit

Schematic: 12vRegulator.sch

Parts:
C1, C2: C_1uF; C_0603_1608Metric; Digi-Key Part Number 1276-1102-1-ND
D1: 1N5819; D_SOD-123; Digi-Key Part Number 1N5819HW-FDICT-ND
L1: 10u; IND_LQH43PN100M26L; PARTREV N/A; Digi-Key Part Number 490-12780-1-ND
R1: 21.5k; R_0603_1608Metric; Digi-Key Part Number 1276-4771-1-ND
R2: 1.37k; R_0603_1608Metric; Digi-Key Part Number RMCF0603FT1K37CT-ND
R3: 1.13k; R_0603_1608Metric; Digi-Key Part Number RMCF0603FT1K13CT-ND
U1: AP3012KTR-G1; SOT95P280X145-5N; PARTREV 1.6; Digi-Key Part Number AP3012KTR-G1DICT-ND

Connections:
/12vRegulator/Vin: C1.1, L1.1, U1.5; also elsewhere on the board
/12vRegulator/Vout: C2.1, D1.1, R1.1; also elsewhere on the board
GND: C1.2, C2.2, R3.2, U1.2; also elsewhere on the board
unnamed: D1.2, L1.2, U1.1
unnamed: R1.2, R2.1, U1.3
unnamed: R2.2, R3.1
SHDN: U1.4; also elsewhere on the board

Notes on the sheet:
VOUT=1.25*(1+R1/(R2+R3))=1.25*(1+8.6)=12V Diode rated for 1A Regulator rated for 500mA

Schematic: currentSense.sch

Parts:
C3, C4, C7: DNP; C_0603_1608Metric_DNP
C5: C_0.1uF; C_0603_1608Metric; Digi-Key Part Number 1276-1006-1-ND
C6: C_1uF; C_0603_1608Metric; Digi-Key Part Number 1276-1102-1-ND
R4, R5: NetTie; R_0603_1608Metric_NetTie
TP1, TP2, TP3, TP4, TP5, TP6, TP7: TestPoint_SMDpad; TestPoint_Pad_D2.0mm
U3: INA250A3PWR; SOP65P640X120-16N; Digi-Key Part Number 296-43803-1-ND

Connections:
/currentSense/IN+: TP3.1, U3.14, U3.15, U3.16; also elsewhere on the board
/currentSense/OUT: TP7.1, U3.9; also elsewhere on the board
/currentSense/VS: C5.2, C6.2, TP4.1, U3.10; also elsewhere on the board
GND: C3.2, C5.1, C6.1, C7.2, TP1.1, U3.6, U3.7, U3.8, U3.11; also elsewhere on the board
unnamed: C3.1, C4.1, R4.1, TP2.1, U3.12
unnamed: C4.2, C7.1, R5.2, TP6.1, U3.5
unnamed: R4.2, U3.13
unnamed: R5.1, U3.4
WirelssModule_Vin: TP5.1, U3.1, U3.2, U3.3; also elsewhere on the board

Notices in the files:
parts and their libraries:
Copyright 2021 Accelerated Designs. All rights reserved.
